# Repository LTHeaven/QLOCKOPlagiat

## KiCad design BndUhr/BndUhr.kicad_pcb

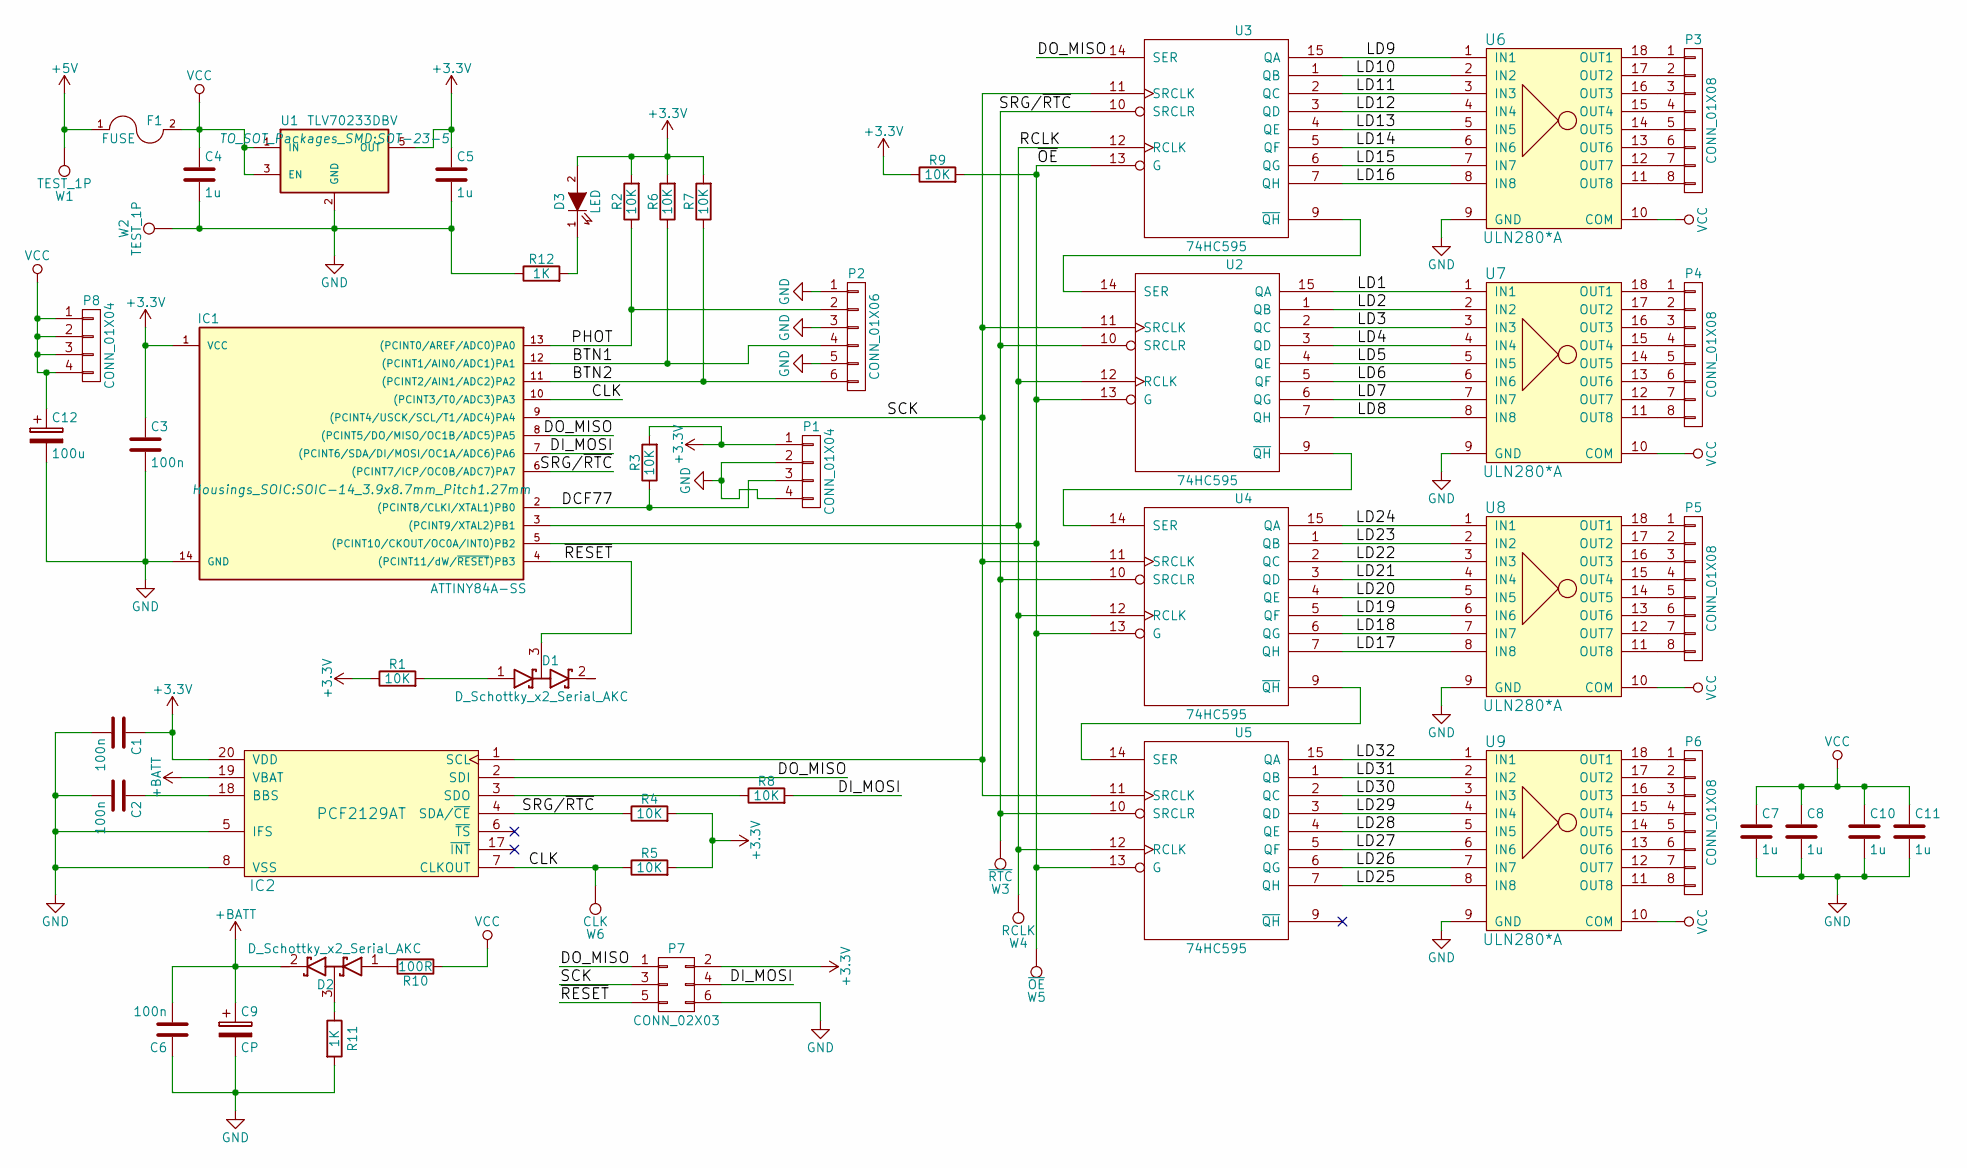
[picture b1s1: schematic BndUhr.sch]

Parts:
C1, C2, C3, C6: 100n; C_0603
C4, C5, C7, C8, C10, C11: 1u; C_0603
C9: CP; Panasonic-SuperCap-20mm
C12: 100u; CP_Radial_D8.0mm_P5.00mm
D1, D2: D_Schottky_x2_Serial_AKC; SOT-23
D3: LED; LED_1206
F1: FUSE; Fuseholder5x20_horiz_open_universal_Type-III
IC1: ATTINY84A-SS; SOIC-14_3.9x8.7mm_Pitch1.27mm
IC2: PCF2129AT; SOIC-20W_7.5x12.8mm_Pitch1.27mm
P1, P8: CONN_01X04; Pin_Header_Straight_1x04_Pitch2.54mm
P2: CONN_01X06; Pin_Header_Straight_1x06_Pitch2.54mm
P3, P4, P5, P6: CONN_01X08; Pin_Header_Angled_1x08_Pitch2.54mm
P7: CONN_02X03; IDC_Header_Straight_6pins
R1, R2, R3, R4, R5, R6, R7, R8, R9: 10K; R_0603
R10: 100R; R_0603
R11, R12: 1K; R_0603
U1: TLV70233DBV; SOT-23-5
U2, U3, U4, U5: 74HC595; SOIC-16_3.9x9.9mm_Pitch1.27mm
U6, U7, U8, U9: ULN280*A; DIP-18_W7.62mm
W1, W2: TEST_1P; SolderWirePad_single_2-5mmDrill
W3: ~RTC; Measurement_Point_Round-SMD-Pad_Small
W4: RCLK; Measurement_Point_Round-SMD-Pad_Small
W5: ~OE; Measurement_Point_Round-SMD-Pad_Small
W6: CLK; Measurement_Point_Round-SMD-Pad_Small

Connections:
+3V3: C1.1, C3.1, C5.1, D3.2 (A), IC1.1 (VCC), IC2.20 (VDD), P1.1, P7.2, R1.1, R2.2, R3.2, R4.2, R5.2, R6.2, R7.2, R9.1, U1.5 (OUT)
+5V: F1.1, W1.1
+BATT: C6.2, C9.1, D2.2 (K), IC2.19 (VBAT)
/BTN1: IC1.12 ((PCINT1/AIN0/ADC1)PA1), P2.4, R6.1
/BTN2: IC1.11 ((PCINT2/AIN1/ADC2)PA2), P2.6, R7.1
/CLK: IC1.10 ((PCINT3/T0/ADC3)PA3), IC2.7 (CLKOUT), R5.1, W6.1
/DCF77: IC1.2 ((PCINT8/CLKI/XTAL1)PB0), P1.3, R3.1
/DI_MOSI: IC1.7 ((PCINT6/SDA/DI/MOSI/OC1A/ADC6)PA6), P7.4, R8.2
/DO_MISO: IC1.8 ((PCINT5/DO/MISO/OC1B/ADC5)PA5), IC2.2 (SDI), P7.1, U3.14 (SER)
/LD1: U2.15 (QA), U7.1 (IN1)
/LD2: U2.1 (QB), U7.2 (IN2)
/LD3: U2.2 (QC), U7.3 (IN3)
/LD4: U2.3 (QD), U7.4 (IN4)
/LD5: U2.4 (QE), U7.5 (IN5)
/LD6: U2.5 (QF), U7.6 (IN6)
/LD7: U2.6 (QG), U7.7 (IN7)
/LD8: U2.7 (QH), U7.8 (IN8)
/LD9: U3.15 (QA), U6.1 (IN1)
/LD10: U3.1 (QB), U6.2 (IN2)
/LD11: U3.2 (QC), U6.3 (IN3)
/LD12: U3.3 (QD), U6.4 (IN4)
/LD13: U3.4 (QE), U6.5 (IN5)
/LD14: U3.5 (QF), U6.6 (IN6)
/LD15: U3.6 (QG), U6.7 (IN7)
/LD16: U3.7 (QH), U6.8 (IN8)
/LD17: U4.7 (QH), U8.8 (IN8)
/LD18: U4.6 (QG), U8.7 (IN7)
/LD19: U4.5 (QF), U8.6 (IN6)
/LD20: U4.4 (QE), U8.5 (IN5)
/LD21: U4.3 (QD), U8.4 (IN4)
/LD22: U4.2 (QC), U8.3 (IN3)
/LD23: U4.1 (QB), U8.2 (IN2)
/LD24: U4.15 (QA), U8.1 (IN1)
/LD25: U5.7 (QH), U9.8 (IN8)
/LD26: U5.6 (QG), U9.7 (IN7)
/LD27: U5.5 (QF), U9.6 (IN6)
/LD28: U5.4 (QE), U9.5 (IN5)
/LD29: U5.3 (QD), U9.4 (IN4)
/LD30: U5.2 (QC), U9.3 (IN3)
/LD31: U5.1 (QB), U9.2 (IN2)
/LD32: U5.15 (QA), U9.1 (IN1)
/PHOT: IC1.13 ((PCINT0/AREF/ADC0)PA0), P2.2, R2.1
/RCLK: IC1.3 ((PCINT9/XTAL2)PB1), U2.12 (RCLK), U3.12 (RCLK), U4.12 (RCLK), U5.12 (RCLK), W4.1
/SCK: IC1.9 ((PCINT4/USCK/SCL/T1/ADC4)PA4), IC2.1 (SCL), P7.3, U2.11 (SRCLK), U3.11 (SRCLK), U4.11 (SRCLK), U5.11 (SRCLK)
/SRG/~RTC: IC1.6 ((PCINT7/ICP/OC0B/ADC7)PA7), IC2.4 (SDA/~CE), R4.1, U2.10 (SRCLR), U3.10 (SRCLR), U4.10 (SRCLR), U5.10 (SRCLR), W3.1
/~OE: IC1.5 ((PCINT10/CKOUT/OC0A/INT0)PB2), R9.2, U2.13 (G), U3.13 (G), U4.13 (G), U5.13 (G), W5.1
/~RESET: D1.3 (common), IC1.4 ((PCINT11/dW/~RESET~)PB3), P7.5
GND: C1.2, C2.2, C3.2, C4.2, C5.2, C6.1, C7.2, C8.2, C9.2, C10.2, C11.2, C12.2, IC1.14 (GND), IC2.5 (IFS), IC2.8 (VSS), P1.2, P1.4, P2.1, P2.3, P2.5, P7.6, R11.2, R12.1, U1.2 (GND), U2.8 (GND), U3.8 (GND), U4.8 (GND), U5.8 (GND), U6.9 (GND), U7.9 (GND), U8.9 (GND), U9.9 (GND), W2.1
unnamed: C2.1, IC2.18 (BBS)
unnamed: D1.1 (A), R1.2
unnamed: D2.1 (A), R10.2
unnamed: D2.3 (common), R11.1
unnamed: D3.1 (K), R12.2
unnamed: IC2.3 (SDO), R8.1
unnamed: P3.1, U6.18 (OUT1)
unnamed: P3.2, U6.17 (OUT2)
unnamed: P3.3, U6.16 (OUT3)
unnamed: P3.4, U6.15 (OUT4)
unnamed: P3.5, U6.14 (OUT5)
unnamed: P3.6, U6.13 (OUT6)
unnamed: P3.7, U6.12 (OUT7)
unnamed: P3.8, U6.11 (OUT8)
unnamed: P4.1, U7.18 (OUT1)
unnamed: P4.2, U7.17 (OUT2)
unnamed: P4.3, U7.16 (OUT3)
unnamed: P4.4, U7.15 (OUT4)
unnamed: P4.5, U7.14 (OUT5)
unnamed: P4.6, U7.13 (OUT6)
unnamed: P4.7, U7.12 (OUT7)
unnamed: P4.8, U7.11 (OUT8)
unnamed: P5.1, U8.18 (OUT1)
unnamed: P5.2, U8.17 (OUT2)
unnamed: P5.3, U8.16 (OUT3)
unnamed: P5.4, U8.15 (OUT4)
unnamed: P5.5, U8.14 (OUT5)
unnamed: P5.6, U8.13 (OUT6)
unnamed: P5.7, U8.12 (OUT7)
unnamed: P5.8, U8.11 (OUT8)
unnamed: P6.1, U9.18 (OUT1)
unnamed: P6.2, U9.17 (OUT2)
unnamed: P6.3, U9.16 (OUT3)
unnamed: P6.4, U9.15 (OUT4)
unnamed: P6.5, U9.14 (OUT5)
unnamed: P6.6, U9.13 (OUT6)
unnamed: P6.7, U9.12 (OUT7)
unnamed: P6.8, U9.11 (OUT8)
unnamed: U2.9 (~QH), U4.14 (SER)
unnamed: U2.14 (SER), U3.9 (~QH)
unnamed: U4.9 (~QH), U5.14 (SER)
VCC: C4.1, C7.1, C8.1, C10.1, C11.1, C12.1, F1.2, P8.1, P8.2, P8.3, P8.4, R10.1, U1.1 (IN), U1.3 (EN), U2.16 (VCC), U3.16 (VCC), U4.16 (VCC), U5.16 (VCC), U6.10 (COM), U7.10 (COM), U8.10 (COM), U9.10 (COM)

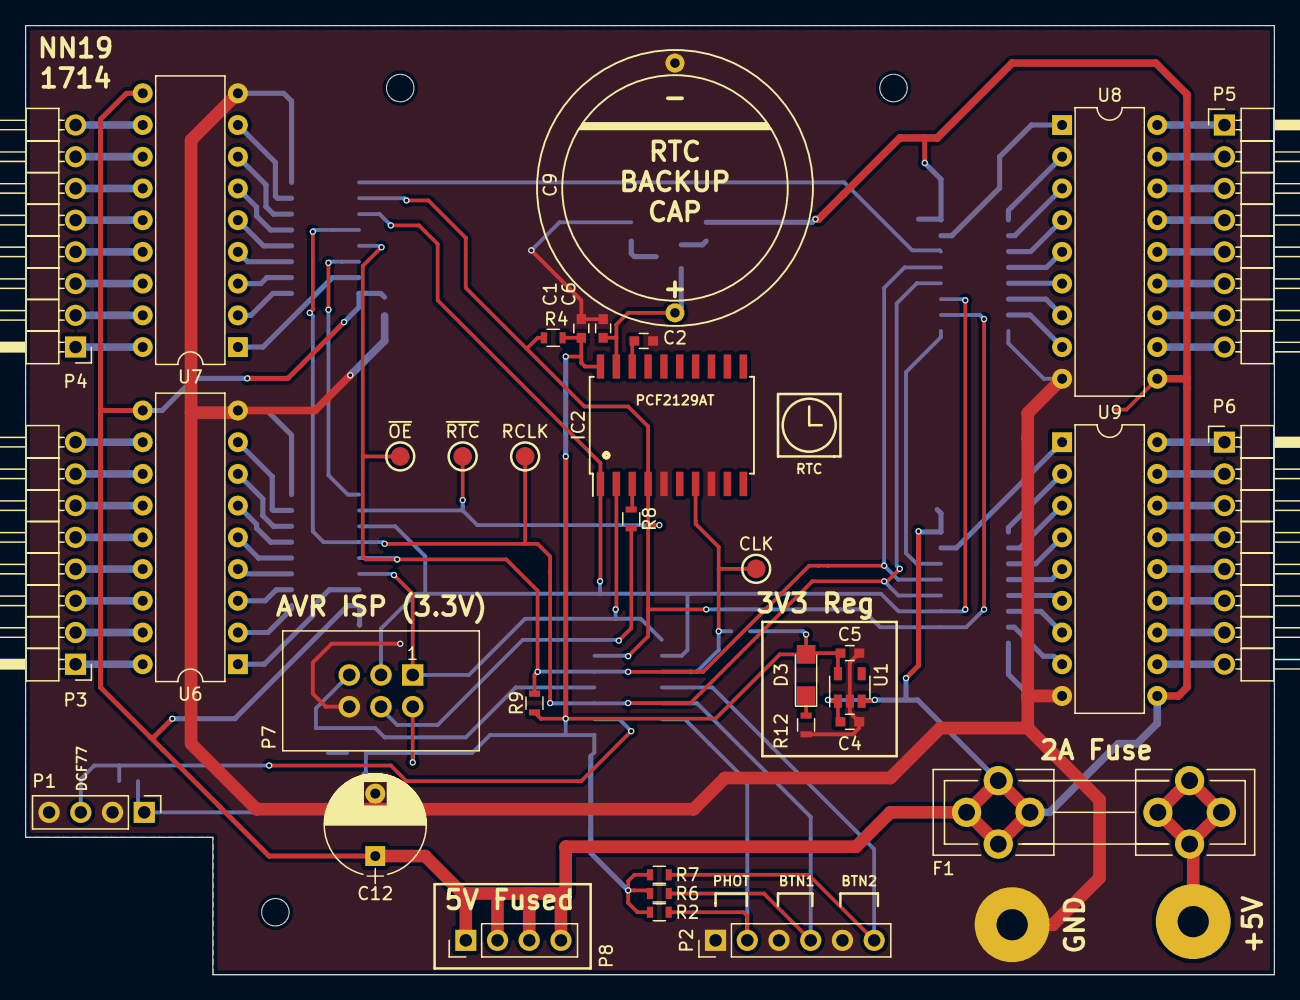
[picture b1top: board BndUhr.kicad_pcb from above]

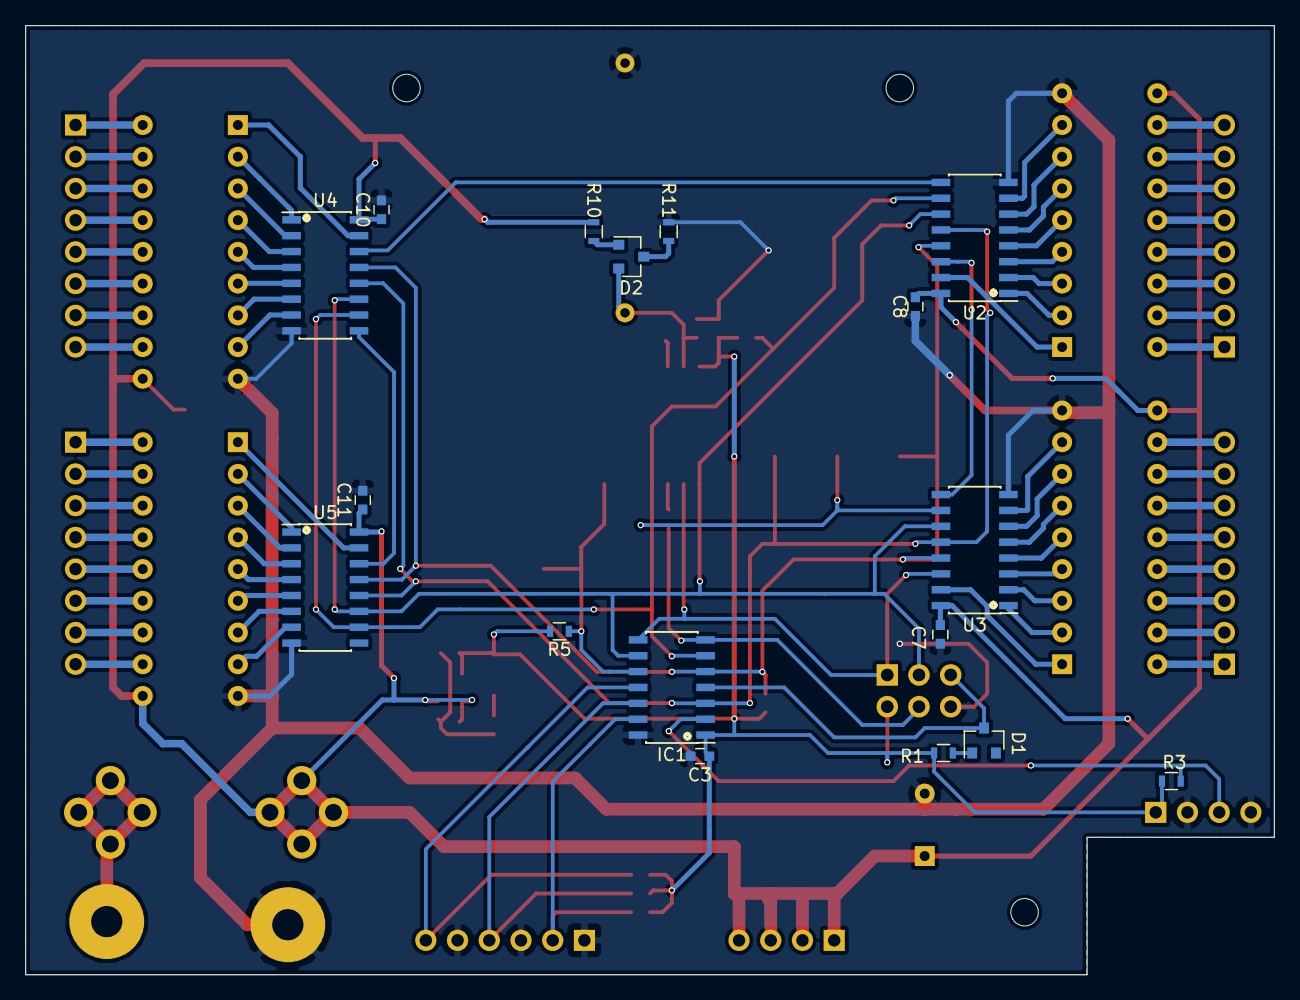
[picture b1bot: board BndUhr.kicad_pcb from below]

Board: 2 copper layers, 100.0 x 76.0 mm, 53 parts (17 on the bottom side), 90 nets.

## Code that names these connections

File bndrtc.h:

#include <avr/io.h>

#define F_CPU 4000000UL
#include <util/delay.h>

#define PA_OUT_SREG PA7
#define PA_OUT_SCL PA4
#define PA_OUT_DO PA5

#define PB_OUT_OEN PB2
#define PB_OUT_RCK PB1

#define PIN_DCF (PINB & 1) // PB0

#define DDRA_INIT (1 << PA_OUT_SREG) | (1 << PA_OUT_SCL) | (1 << PA_OUT_DO)
#define DDRB_INIT (1 << PB_OUT_OEN) | (1 << PB_OUT_RCK)

#define SPI_SELECT_SREG PORTA |= (1 << PA_OUT_SREG)
#define SPI_SELECT_RTC PORTA &= ~(1 << PA_OUT_SREG)

#define RTC_REG_SEC 0x03
#define RTC_REG_CKO 0x0F
#define RTC_REG_YEA 0x09

#define PWM_ENABLE TCCR0A = _BV(COM0A1) | _BV(WGM01) | _BV(WGM00)
#define PWM_DISABLE TCCR0A = _BV(WGM01) | _BV(WGM00)

#define DCF_STAT_FIND_SIGNAL 0
#define DCF_STAT_CHECK_PHASE 1
#define DCF_STAT_WAIT_FOR_SYNC 3
#define DCF_STAT_RECEIVING 7
#define DCF_STAT_SUCCESS 15

#define PIN_ES_IST 	(1UL<<0)
#define PIN_FUENF_1 (1UL<<1)
#define PIN_ZEHN_1 	(1UL<<2)
#define PIN_ZWANZIG (1UL<<3)
#define PIN_VIERTEL (1UL<<4)
#define PIN_VOR 	(1UL<<5)
#define PIN_FUNK 	(1UL<<6)
#define PIN_NACH 	(1UL<<7)
#define PIN_HALB 	(1UL<<8)
#define PIN_EL 		(1UL<<9)
#define PIN_F 		(1UL<<10)
#define PIN_UENF 	(1UL<<11)
#define PIN_EIN 	(1UL<<12)
#define PIN_S 		(1UL<<13)
#define PIN_ZWEI 	(1UL<<14)
#define PIN_DREI 	(1UL<<15)
#define PIN_VIER 	(1UL<<16)
#define PIN_SECHS 	(1UL<<17)
#define PIN_ACHT 	(1UL<<18)
#define PIN_SIEBEN 	(1UL<<19)
#define PIN_ZWOELF 	(1UL<<20)
#define PIN_ZEH 	(1UL<<21)
#define PIN_N 		(1UL<<22)
#define PIN_EUN 	(1UL<<23)
#define PIN_UHR 	(1UL<<24)

#define PIN_ELF 	(PIN_EL | PIN_F)
#define PIN_FUENF_2 (PIN_F | PIN_UENF)
#define PIN_EINS 	(PIN_EIN | PIN_S)
#define PIN_ZEHN_2 	(PIN_ZEH | PIN_N)
#define PIN_NEUN 	(PIN_N | PIN_EUN)

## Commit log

2018-09-15 current status
2018-09-15 implemented time display logic (hopefully)
2018-09-15 removed debug since time is now displayed correctly (hopefully)
2018-09-15 could not work, implemented correct dcf77 handling
2018-09-15 fuck
2018-09-15 implemented RTC write and some DEBUG SHIT
2018-09-15 reimplemented parity check
2018-09-15 switched to rtc board use, added funk info
2018-09-15 testing time reset
2018-09-15 changed sync time to 3AM
2018-09-23 added board stuff
2019-07-11 formatting
